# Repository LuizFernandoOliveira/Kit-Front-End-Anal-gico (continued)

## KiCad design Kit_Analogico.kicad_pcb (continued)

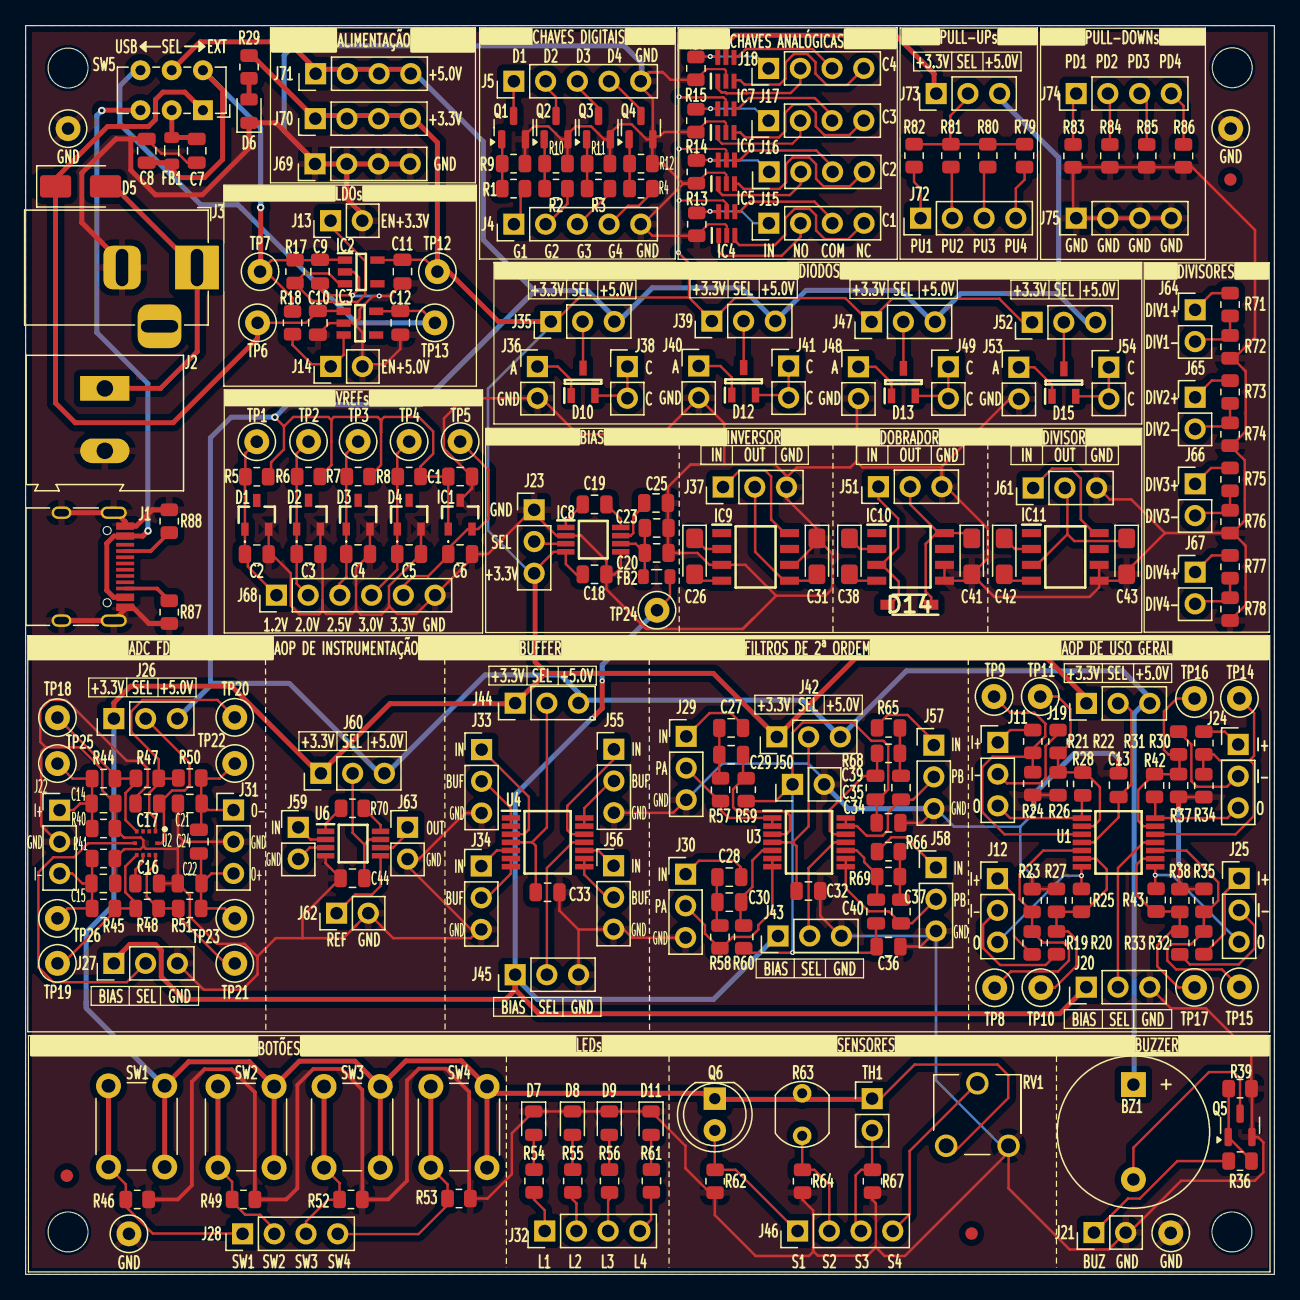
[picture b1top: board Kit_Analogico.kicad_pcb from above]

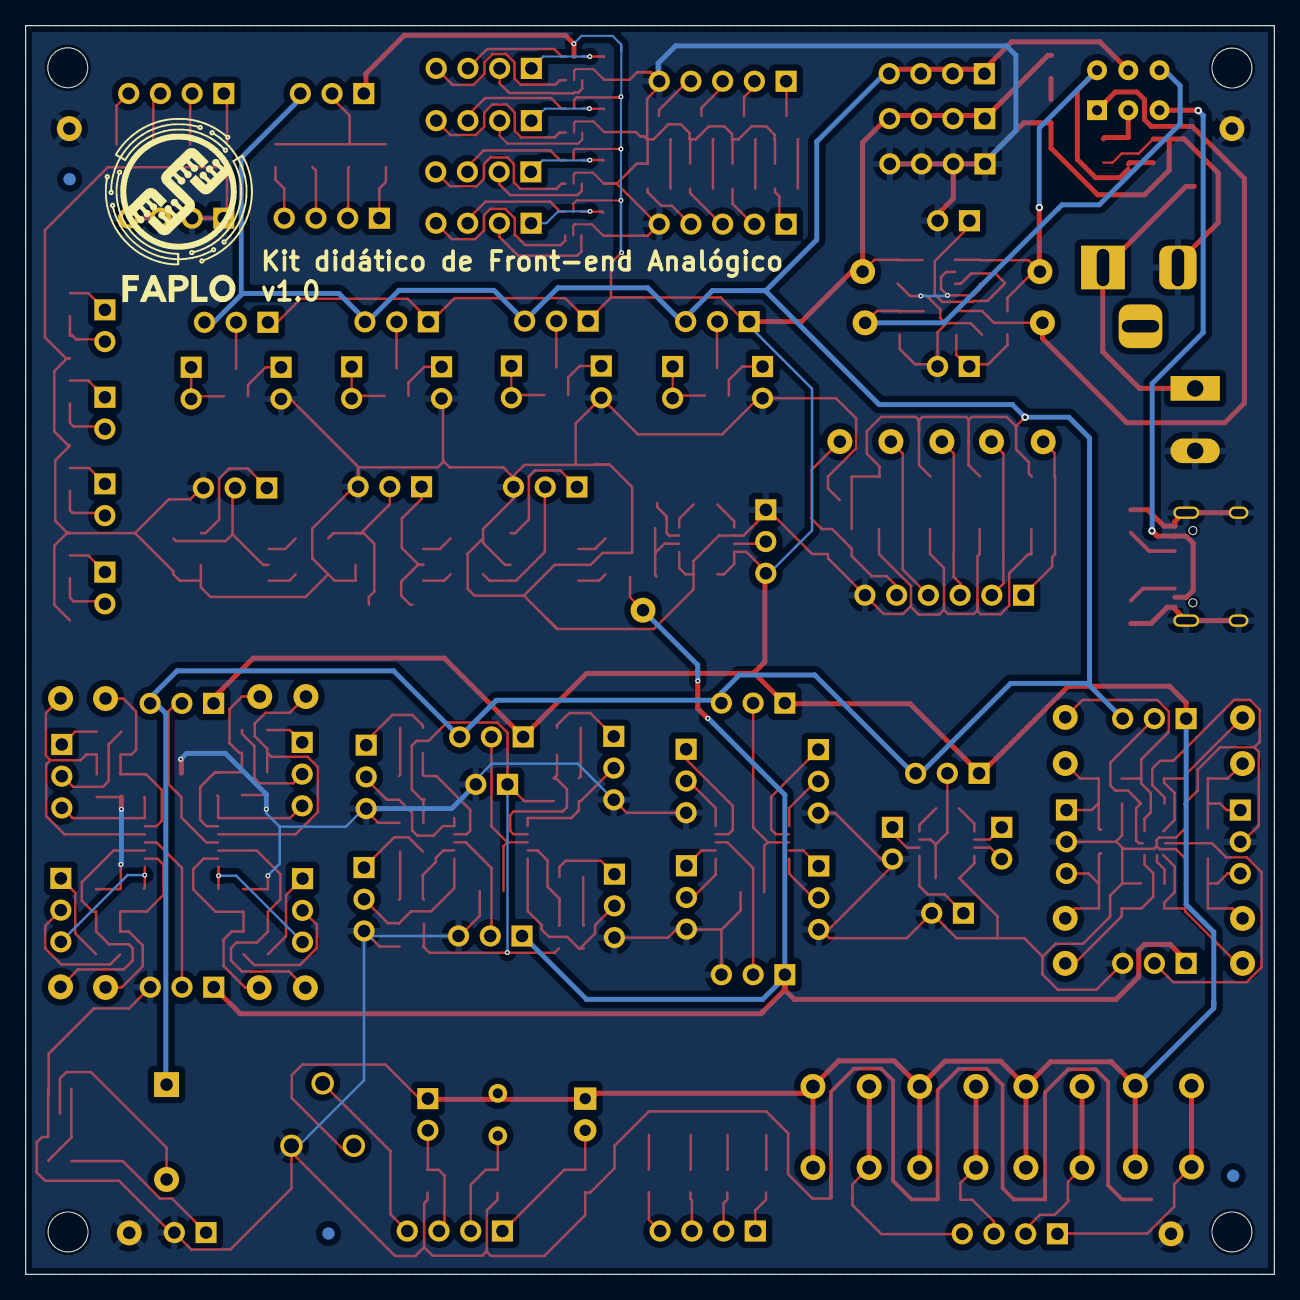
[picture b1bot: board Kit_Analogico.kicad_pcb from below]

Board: 2 copper layers, 100.0 x 100.0 mm, 289 parts (3 on the bottom side), 182 nets.

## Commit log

2026-04-17 Inicialização de repositório
2026-04-17 Enhance README with project details and badges
    Added project status badges, detailed description, technical specifications, repository structure, and author information to the README.
2026-04-17 Add LICENSE file with CC BY-NC-ND 4.0
    Added Creative Commons Attribution-NonCommercial-NoDerivatives 4.0 International Public License to the project.
